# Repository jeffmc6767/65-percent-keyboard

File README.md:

67% Keyboard
-
A 60-70% keyboard with a customizable oled and 2 rotary encoders. 

Quick start
-

How can you build it yourself. 

1. Buy all the parts in the BOM (Also make sure to buy Cherry MX switches that are 3 or 5 pin) and order a PCB
2. solder everything according to the layout on the PCB
3. Install firmware by plugging in the raspberry pi pico 2wh and flashing it.
4. Customize keys in the software
5. Done!

Features:
-

1. 73 key keyboard, with 2 customizable keys
2. 2 rotary encoders for volume and brightness control(default)
3. Rotary encoders include push button
4. 1 0.91" customizable OLED screen

How it works:
-

The 73 switches and 2 rotary encoders are wired in a matrix, each with a diode to detect which key is pressed. Each switch is soldered directly to the PCB. 

The keyboard will be wireless via bluetooth, 2.4gz, and also supports USBC connection, since the raspberry pi pico2wh has wifi and bluetooth connectivity. 

Here's some images:
-

I will be using PLA matte white to print the case out (because it has no LED's) or petg white depending on what filament I have. 

ROUGH BOM: look at the BOM.csv. 

- 73x switches: $29.99(I own these already)
- 75x 1N4148 Diodes: $5
- 2x PEC11R-4220f-S0024-ND: $8.60
- 1x Raspberry Pi Pico 2WH: $21
- 1x 0.91" OLED: $9
- 1x Tin Lead Sn60-Pb40 (0.6mm, 50g): $12
- 1x PCB: $76
- 6.25U and 2.00U stabilizer: $15

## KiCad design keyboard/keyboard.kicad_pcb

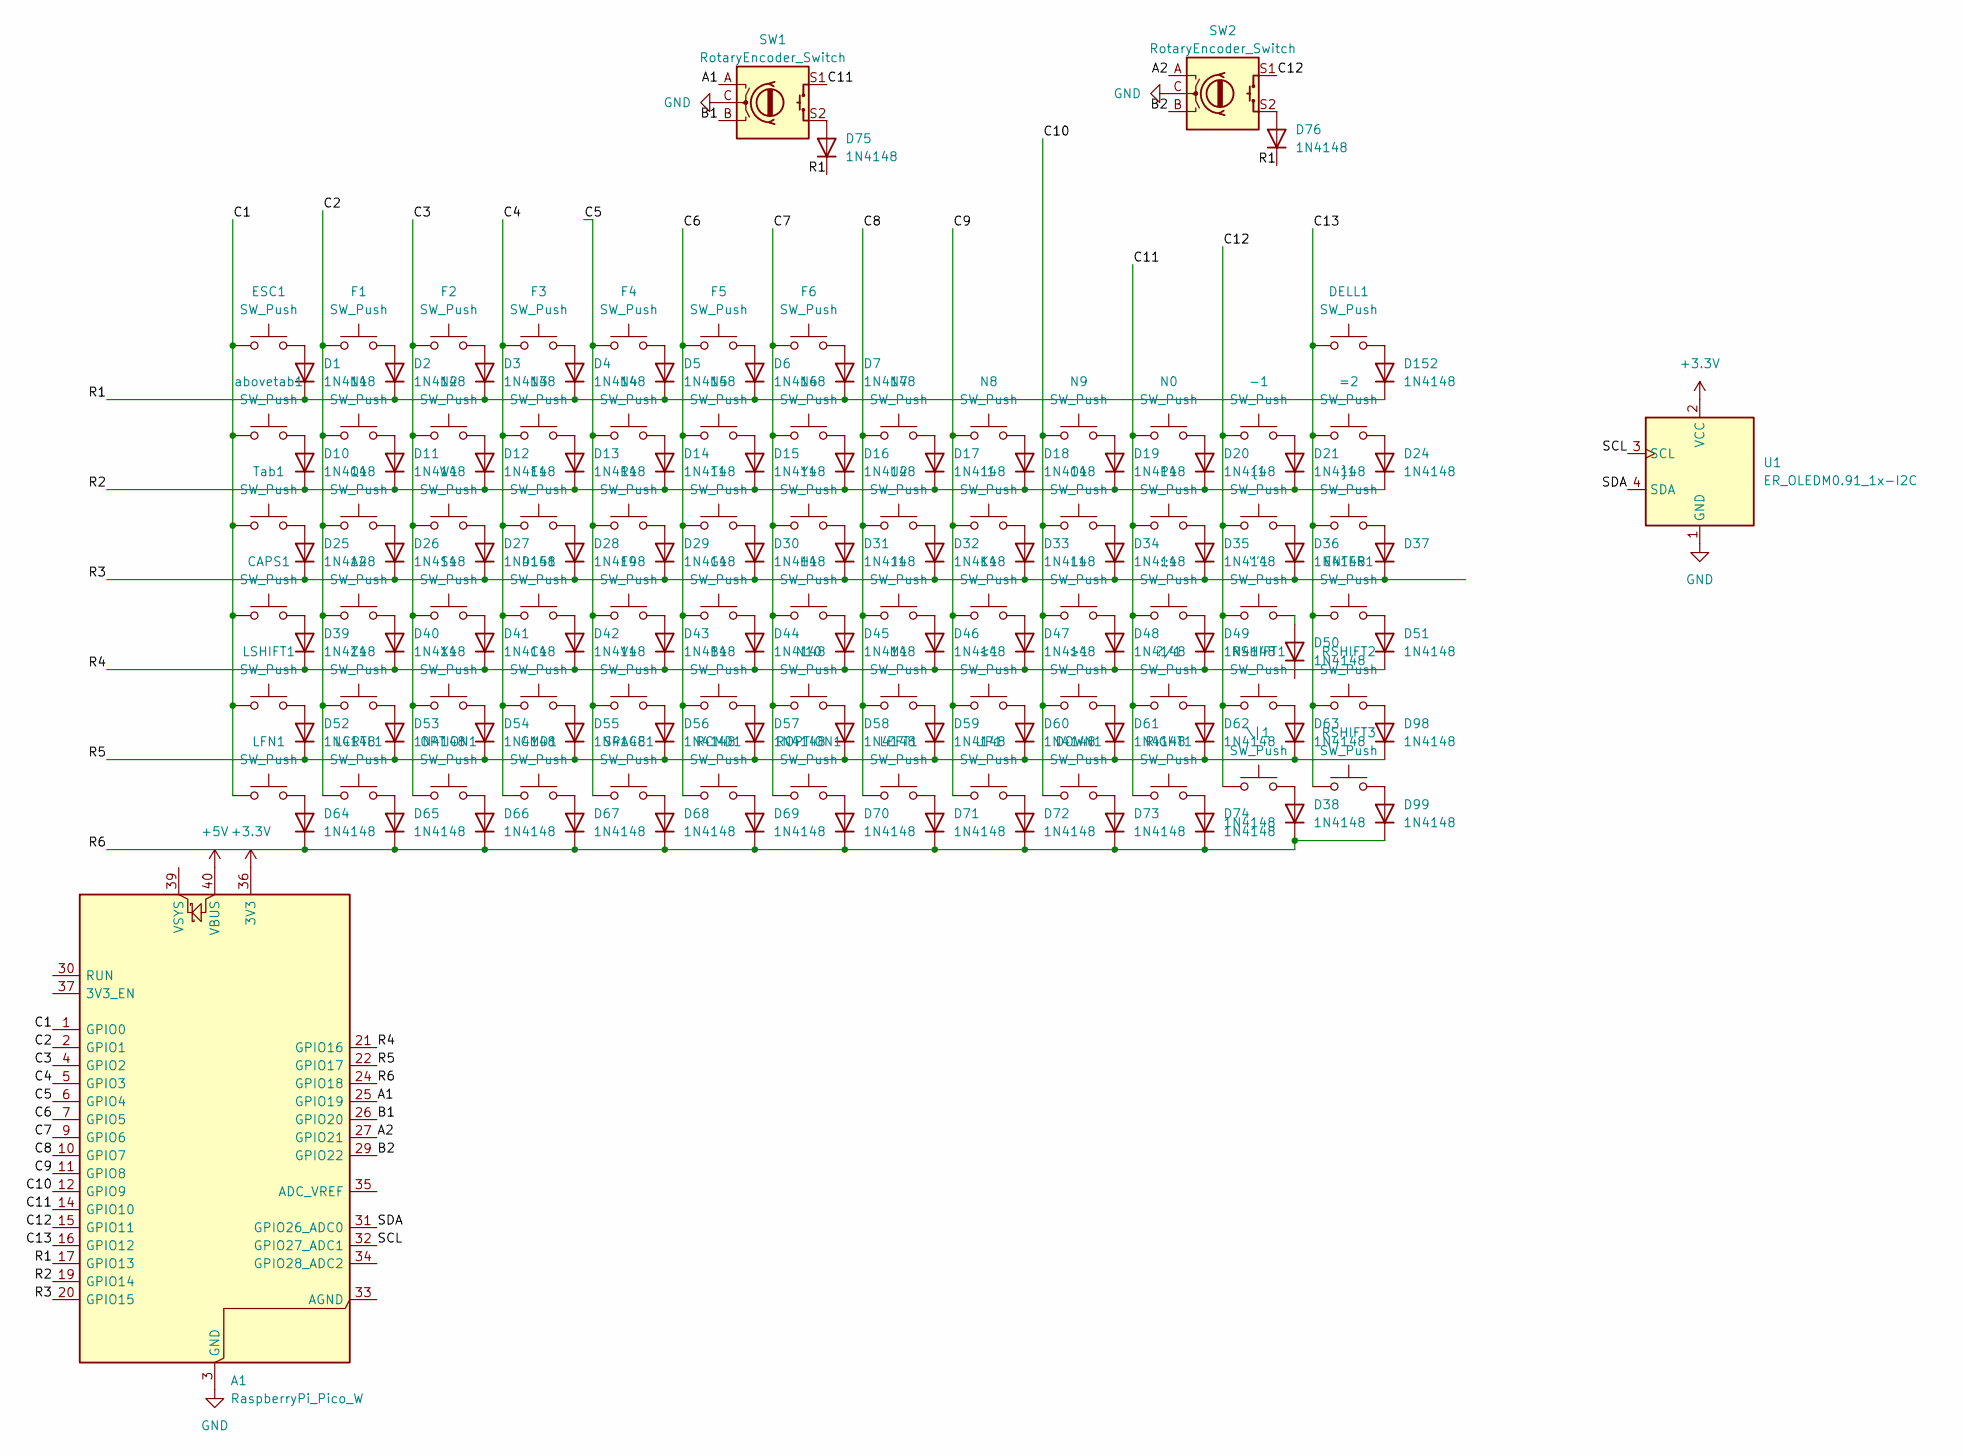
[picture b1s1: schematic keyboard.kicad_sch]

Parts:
"'1: SW_Push; SW_Cherry_MX_1.00u_PCB-Gateron-KS-3x switch
-1: SW_Push; SW_Cherry_MX_1.00u_PCB-Gateron-KS-3x switch
:;1: SW_Push; SW_Cherry_MX_1.00u_PCB-Gateron-KS-3x switch
<1: SW_Push; SW_Cherry_MX_1.00u_PCB-Gateron-KS-3x switch
=2: SW_Push; SW_Cherry_MX_1.00u_PCB-Gateron-KS-3x switch
>1: SW_Push; SW_Cherry_MX_1.00u_PCB-Gateron-KS-3x switch
?/1: SW_Push; SW_Cherry_MX_1.00u_PCB-Gateron-KS-3x switch
A1: RaspberryPi_Pico_W; RaspberryPi_Pico_W_SMD_HandSolder
A2: SW_Push; SW_Cherry_MX_1.00u_PCB-Gateron-KS-3x switch
B1: SW_Push; SW_Cherry_MX_1.00u_PCB-Gateron-KS-3x switch
C1: SW_Push; SW_Cherry_MX_1.00u_PCB-Gateron-KS-3x switch
CAPS1: SW_Push; SW_Cherry_MX_1.75u_PCB-Gateron-KS-3X
CMD1: SW_Push; SW_Cherry_MX_1.25u_PCB-Gateron-KS-3X
D1, D2, D3, D4, D5, D6, D7, D10, D11, D12, D13, D14, D15, D16, D17, D18, D19, D20, D21, D24, D25, D26, D27, D28, D29, D30, D31, D32, D33, D34, D35, D36, D37, D38, D39, D40, D41, D42, D43, D44, D45, D46, D47, D48, D49, D50, D51, D52, D53, D54, D55, D56, D57, D58, D59, D60, D61, D62, D63, D64, D65, D66, D67, D68, D69, D70, D71, D72, D73, D74, D75, D76, D98, D99, D152: 1N4148; D_DO-35_SOD27_P7.62mm_Horizontal
D151: SW_Push; SW_Cherry_MX_1.00u_PCB-Gateron-KS-3x switch
DELL1: SW_Push; SW_Cherry_MX_1.50u_PCB-Gateron-KS-3X
DOWN1: SW_Push; SW_Cherry_MX_1.00u_PCB-Gateron-KS-3x switch
E1: SW_Push; SW_Cherry_MX_1.00u_PCB-Gateron-KS-3x switch
ENTER1: SW_Push; SW_Cherry_MX_1.75u_PCB-Gateron-KS-3X
ESC1: SW_Push; SW_Cherry_MX_1.50u_PCB-Gateron-KS-3X
F1, F2, F3, F4, F5, F6, F9: SW_Push; SW_Cherry_MX_1.00u_PCB-Gateron-KS-3x switch
G1: SW_Push; SW_Cherry_MX_1.00u_PCB-Gateron-KS-3x switch
H1: SW_Push; SW_Cherry_MX_1.00u_PCB-Gateron-KS-3x switch
I1: SW_Push; SW_Cherry_MX_1.00u_PCB-Gateron-KS-3x switch
J1: SW_Push; SW_Cherry_MX_1.00u_PCB-Gateron-KS-3x switch
K1: SW_Push; SW_Cherry_MX_1.00u_PCB-Gateron-KS-3x switch
L1: SW_Push; SW_Cherry_MX_1.00u_PCB-Gateron-KS-3x switch
LCRTL1: SW_Push; SW_Cherry_MX_1.00u_PCB-Gateron-KS-3x switch
LEFT1: SW_Push; SW_Cherry_MX_1.00u_PCB-Gateron-KS-3x switch
LFN1: SW_Push; SW_Cherry_MX_1.00u_PCB-Gateron-KS-3x switch
LSHIFT1: SW_Push; SW_Cherry_MX_2.25u_PCB-Gateron-KS-3X
M1: SW_Push; SW_Cherry_MX_1.00u_PCB-Gateron-KS-3x switch
N0, N1, N2, N3, N4, N5, N6, N7, N8, N9, N10: SW_Push; SW_Cherry_MX_1.00u_PCB-Gateron-KS-3x switch
O1: SW_Push; SW_Cherry_MX_1.00u_PCB-Gateron-KS-3x switch
OPTION1: SW_Push; SW_Cherry_MX_1.00u_PCB-Gateron-KS-3x switch
P1: SW_Push; SW_Cherry_MX_1.00u_PCB-Gateron-KS-3x switch
Q1: SW_Push; SW_Cherry_MX_1.00u_PCB-Gateron-KS-3x switch
R1: SW_Push; SW_Cherry_MX_1.00u_PCB-Gateron-KS-3x switch
RCMD1: SW_Push; SW_Cherry_MX_1.25u_PCB-Gateron-KS-3X
RIGHT1: SW_Push; SW_Cherry_MX_1.00u_PCB-Gateron-KS-3x switch
ROPTION1: SW_Push; SW_Cherry_MX_1.00u_PCB-Gateron-KS-3x switch
RSHIFT1: SW_Push; SW_Cherry_MX_1.75u_PCB-Gateron-KS-3X
RSHIFT2, RSHIFT3: SW_Push; SW_Cherry_MX_1.00u_PCB-Gateron-KS-3x switch
S1: SW_Push; SW_Cherry_MX_1.00u_PCB-Gateron-KS-3x switch
SPACE1: SW_Push; SW_Cherry_MX_6.25u_PCB-Gateron-KS-3X-switch
SW1, SW2: RotaryEncoder_Switch; RotaryEncoder_Alps_EC11E-Switch_Vertical_H20mm
T1: SW_Push; SW_Cherry_MX_1.00u_PCB-Gateron-KS-3x switch
Tab1: SW_Push; SW_Cherry_MX_1.50u_PCB-Gateron-KS-3X
U1: ER_OLEDM0.91_1x-I2C
U2: SW_Push; SW_Cherry_MX_1.00u_PCB-Gateron-KS-3x switch
UP1: SW_Push; SW_Cherry_MX_1.00u_PCB-Gateron-KS-3x switch
V1: SW_Push; SW_Cherry_MX_1.00u_PCB-Gateron-KS-3x switch
W1: SW_Push; SW_Cherry_MX_1.00u_PCB-Gateron-KS-3x switch
X1: SW_Push; SW_Cherry_MX_1.00u_PCB-Gateron-KS-3x switch
Y1: SW_Push; SW_Cherry_MX_1.00u_PCB-Gateron-KS-3x switch
Z1: SW_Push; SW_Cherry_MX_1.00u_PCB-Gateron-KS-3x switch
\|1: SW_Push; SW_Cherry_MX_1.00u_PCB-Gateron-KS-3x switch
abovetab1: SW_Push; SW_Cherry_MX_1.00u_PCB-Gateron-KS-3x switch
{1: SW_Push; SW_Cherry_MX_1.00u_PCB-Gateron-KS-3x switch
}1: SW_Push; SW_Cherry_MX_1.00u_PCB-Gateron-KS-3x switch

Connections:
+3.3V: A1.36 (3V3), U1.2 (VCC)
+5V: A1.40 (VBUS)
/A1: A1.25 (GPIO19), SW1.A
/A2: A1.27 (GPIO21), SW2.A
/B1: A1.26 (GPIO20), SW1.B
/B2: A1.29 (GPIO22), SW2.B
/C1: A1.1 (GPIO0), CAPS1.1, ESC1.1, LFN1.1, LSHIFT1.1, Tab1.1, abovetab1.1
/C2: A1.2 (GPIO1), A2.1, F1.1, LCRTL1.1, N1.1, Q1.1, Z1.1
/C3: A1.4 (GPIO2), F2.1, N2.1, OPTION1.1, S1.1, W1.1, X1.1
/C4: A1.5 (GPIO3), C1.1, CMD1.1, D151.1, E1.1, F3.1, N3.1
/C5: A1.6 (GPIO4), F4.1, F9.1, N4.1, R1.1, SPACE1.1, V1.1
/C6: A1.7 (GPIO5), B1.1, F5.1, G1.1, N5.1, RCMD1.1, T1.1
/C7: A1.9 (GPIO6), F6.1, H1.1, N6.1, N10.1, ROPTION1.1, Y1.1
/C8: A1.10 (GPIO7), J1.1, LEFT1.1, M1.1, N7.1, U2.1
/C9: <1.1, A1.11 (GPIO8), I1.1, K1.1, N8.1, UP1.1
/C10: >1.1, A1.12 (GPIO9), DOWN1.1, L1.1, N9.1, O1.1
/C11: :;1.1, ?/1.1, A1.14 (GPIO10), N0.1, P1.1, RIGHT1.1, SW1.S1
/C12: "'1.1, -1.1, A1.15 (GPIO11), RSHIFT1.1, SW2.S1, \|1.1, {1.1
/C13: =2.1, A1.16 (GPIO12), DELL1.1, ENTER1.1, RSHIFT2.1, RSHIFT3.1, }1.1
/R1: A1.17 (GPIO13), D1.1 (K), D2.1 (K), D3.1 (K), D4.1 (K), D5.1 (K), D6.1 (K), D7.1 (K), D75.1 (K), D76.1 (K), D152.1 (K)
/R2: A1.19 (GPIO14), D10.1 (K), D11.1 (K), D12.1 (K), D13.1 (K), D14.1 (K), D15.1 (K), D16.1 (K), D17.1 (K), D18.1 (K), D19.1 (K), D20.1 (K), D21.1 (K), D24.1 (K)
/R3: A1.20 (GPIO15), D25.1 (K), D26.1 (K), D27.1 (K), D28.1 (K), D29.1 (K), D30.1 (K), D31.1 (K), D32.1 (K), D33.1 (K), D34.1 (K), D35.1 (K), D36.1 (K), D37.1 (K)
/R4: A1.21 (GPIO16), D39.1 (K), D40.1 (K), D41.1 (K), D42.1 (K), D43.1 (K), D44.1 (K), D45.1 (K), D46.1 (K), D47.1 (K), D48.1 (K), D49.1 (K), D51.1 (K)
/R5: A1.22 (GPIO17), D52.1 (K), D53.1 (K), D54.1 (K), D55.1 (K), D56.1 (K), D57.1 (K), D58.1 (K), D59.1 (K), D60.1 (K), D61.1 (K), D62.1 (K), D63.1 (K), D98.1 (K)
/R6: A1.24 (GPIO18), D38.1 (K), D64.1 (K), D65.1 (K), D66.1 (K), D67.1 (K), D68.1 (K), D69.1 (K), D70.1 (K), D71.1 (K), D72.1 (K), D73.1 (K), D74.1 (K), D99.1 (K)
/SCL: A1.32 (GPIO27_ADC1), U1.3 (SCL)
/SDA: A1.31 (GPIO26_ADC0), U1.4 (SDA)
GND: A1.3 (GND), A1.8 (GND), A1.13 (GND), A1.18 (GND), A1.23 (GND), A1.28 (GND), A1.38 (GND), SW1.C, SW2.C, U1.1 (GND)
unnamed: D1.2 (A), ESC1.2
unnamed: D2.2 (A), F1.2
unnamed: D3.2 (A), F2.2
unnamed: D4.2 (A), F3.2
unnamed: D5.2 (A), F4.2
unnamed: D6.2 (A), F5.2
unnamed: D7.2 (A), F6.2
unnamed: D10.2 (A), abovetab1.2
unnamed: D11.2 (A), N1.2
unnamed: D12.2 (A), N2.2
unnamed: D13.2 (A), N3.2
unnamed: D14.2 (A), N4.2
unnamed: D15.2 (A), N5.2
unnamed: D16.2 (A), N6.2
unnamed: D17.2 (A), N7.2
unnamed: D18.2 (A), N8.2
unnamed: D19.2 (A), N9.2
unnamed: D20.2 (A), N0.2
unnamed: -1.2, D21.2 (A)
unnamed: =2.2, D24.2 (A)
unnamed: D25.2 (A), Tab1.2
unnamed: D26.2 (A), Q1.2
unnamed: D27.2 (A), W1.2
unnamed: D28.2 (A), E1.2
unnamed: D29.2 (A), R1.2
unnamed: D30.2 (A), T1.2
unnamed: D31.2 (A), Y1.2
unnamed: D32.2 (A), U2.2
unnamed: D33.2 (A), I1.2
unnamed: D34.2 (A), O1.2
unnamed: D35.2 (A), P1.2
unnamed: D36.2 (A), {1.2
unnamed: D37.2 (A), }1.2
unnamed: D38.2 (A), \|1.2
unnamed: CAPS1.2, D39.2 (A)
unnamed: A2.2, D40.2 (A)
unnamed: D41.2 (A), S1.2
unnamed: D42.2 (A), D151.2
unnamed: D43.2 (A), F9.2
unnamed: D44.2 (A), G1.2
unnamed: D45.2 (A), H1.2
unnamed: D46.2 (A), J1.2
unnamed: D47.2 (A), K1.2
unnamed: D48.2 (A), L1.2
unnamed: :;1.2, D49.2 (A)
unnamed: "'1.2, D50.2 (A_2)
unnamed: D51.2 (A), ENTER1.2
unnamed: D52.2 (A), LSHIFT1.2
unnamed: D53.2 (A), Z1.2
unnamed: D54.2 (A), X1.2
unnamed: C1.2, D55.2 (A)
unnamed: D56.2 (A), V1.2
unnamed: B1.2, D57.2 (A)
unnamed: D58.2 (A), N10.2
unnamed: D59.2 (A), M1.2
unnamed: <1.2, D60.2 (A)
unnamed: >1.2, D61.2 (A)
unnamed: ?/1.2, D62.2 (A)
unnamed: D63.2 (A), RSHIFT1.2
unnamed: D64.2 (A), LFN1.2
unnamed: D65.2 (A), LCRTL1.2
unnamed: D66.2 (A), OPTION1.2
unnamed: CMD1.2, D67.2 (A)
unnamed: D68.2 (A), SPACE1.2
unnamed: D69.2 (A), RCMD1.2
unnamed: D70.2 (A), ROPTION1.2
unnamed: D71.2 (A), LEFT1.2
unnamed: D72.2 (A), UP1.2
unnamed: D73.2 (A), DOWN1.2
unnamed: D74.2 (A), RIGHT1.2
unnamed: D75.2 (A), SW1.S2
unnamed: D76.2 (A), SW2.S2
unnamed: D98.2 (A), RSHIFT2.2
unnamed: D99.2 (A), RSHIFT3.2
unnamed: D152.2 (A), DELL1.2

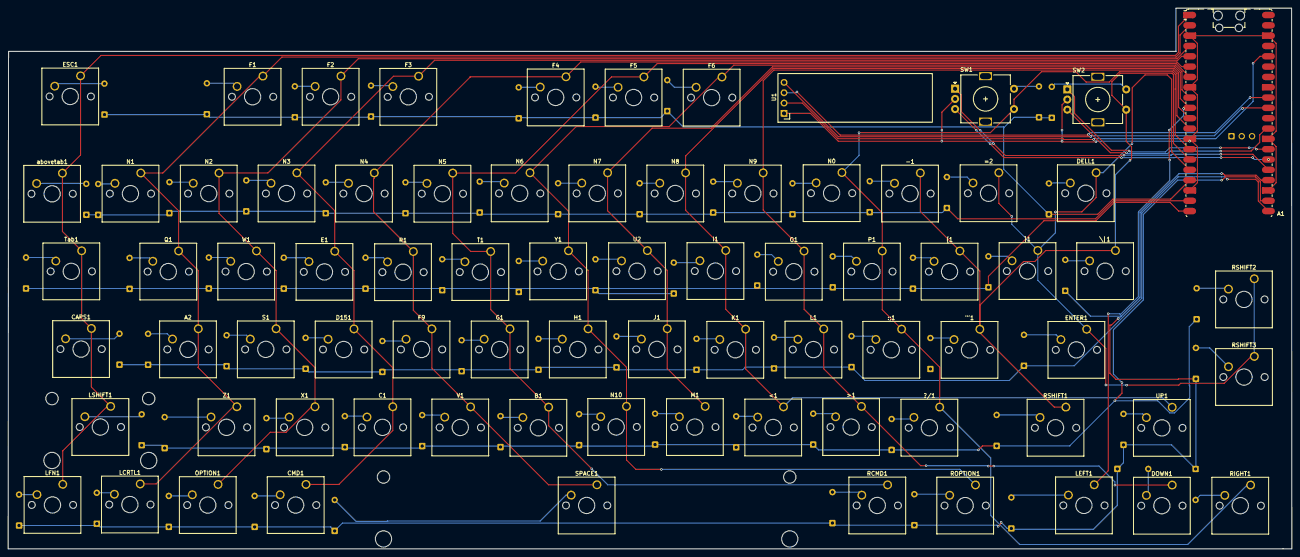
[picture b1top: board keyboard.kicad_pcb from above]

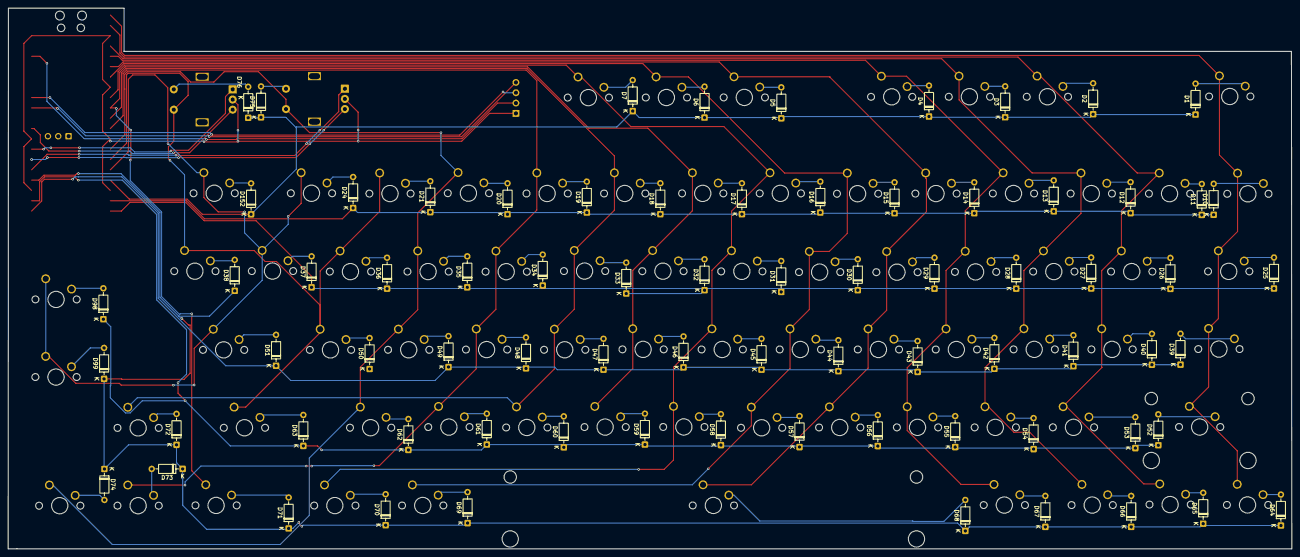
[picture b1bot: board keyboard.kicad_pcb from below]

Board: 2 copper layers, 315.9 x 133.1 mm, 152 parts (75 on the bottom side), 102 nets.

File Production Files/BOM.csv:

"Id";"Designator";"Footprint";"Quantity";"Designation";"Supplier and ref";
1;""'1, -1, :;1, <1, =2, >1, ?/1, A2, abovetab1, B1, C1, D151, DOWN1, E1, F1, F2, F3, F4, F5, F6, F9, G1, H1, I1, J1, K1, L1, LCRTL1, LEFT1, LFN1, M1, N0, N1, N2, N3, N4, N5, N6, N7, N8, N9, N10, O1, OPTION1, P1, Q1, R1, RIGHT1, ROPTION1, RSHIFT2, RSHIFT3, S1, T1, U2, UP1, V1, W1, X1, Y1, Z1, \|1, {1, }1";"SW_Cherry_MX_1.00u_PCB-Gateron-KS-3x switch";63;"SW_Push";;;
2;"A1";"RaspberryPi_Pico_W_SMD_HandSolder";1;"RaspberryPi_Pico_W";;;
3;"CAPS1, ENTER1, RSHIFT1";"SW_Cherry_MX_1.75u_PCB-Gateron-KS-3X";3;"SW_Push";;;
4;"CMD1, RCMD1";"SW_Cherry_MX_1.25u_PCB-Gateron-KS-3X";2;"SW_Push";;;
5;"D1, D2, D3, D4, D5, D6, D7, D10, D11, D12, D13, D14, D15, D16, D17, D18, D19, D20, D21, D24, D25, D26, D27, D28, D29, D30, D31, D32, D33, D34, D35, D36, D37, D38, D39, D40, D41, D42, D43, D44, D45, D46, D47, D48, D49, D50, D51, D52, D53, D54, D55, D56, D57, D58, D59, D60, D61, D62, D63, D64, D65, D66, D67, D68, D69, D70, D71, D72, D73, D74, D75, D76, D98, D99, D152";"D_DO-35_SOD27_P7.62mm_Horizontal";75;"1N4148";;;
6;"DELL1, ESC1, Tab1";"SW_Cherry_MX_1.50u_PCB-Gateron-KS-3X";3;"SW_Push";;;
7;"LSHIFT1";"SW_Cherry_MX_2.25u_PCB-Gateron-KS-3X";1;"SW_Push";;;
8;"SPACE1";"SW_Cherry_MX_6.25u_PCB-Gateron-KS-3X-switch";1;"SW_Push";;;
9;"SW1, SW2";"RotaryEncoder_Alps_EC11E-Switch_Vertical_H20mm";2;"RotaryEncoder_Switch";;;
10;"U1";"ER_OLEDM0.91_1x-I2C";1;"ER_OLEDM0.91_1x-I2C";;;
